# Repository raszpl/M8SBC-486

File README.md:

# M8SBC-486

All the sources (Schematics, PCB, VHDL, BIOS sources) for the M8SBC-486. 

This project is a 486 Homebrew computer, with some efforts to make it kinda PC compatible. See [my page about it](https://maniek86.xyz/projects/m8sbc_486.php).

## Specs:

- 150*150mm 4 layer PCB
- PGA-168 socket for 5V 486 CPUs.
- Xilinx Spartan II XC2S100 FPGA as "chipset". Codename "Hamster 1"
- 4MB SRAM, (8*HM628512)
- 256KB of ROM (W29C020 or 39SF020A) (224 KB accessible)
- 8254 Programmable Interval Timer
- 8259 Programmable Interrupt Controller
- Two 16-bit ISA slots
- PS/2 Keyboard port. Controller is implemented in the FPGA
- Simple CMOS RTC and CMOS storage. Implemented in the FPGA too
- ATMega128 as reset circuit handler, nonvolatile CMOS storage and bitstream loader.

The FSB frequency is currently set to a fixed 24 MHz (DX2 CPUs run then at 48 MHz), but this can be changed by uncommenting/commenting lines in the FPGA source.

Secondary PIC and DMA are missing, so the compatibility is not full. The missing DMA especially breaks support for sound cards.

## Current progress:

The hardware and FPGA are mostly done. BIOS is capable of booting DOS. There are a few issues & bugs, but they are being slowly fixed.

Among the most impressive things the board (as time of writing: 14/03/2026) is capable of: 

- Booting Linux (2.2.26) ([using custom bootloader](https://github.com/maniekx86/linux_m8sbc_boot))

- Booting MS-DOS and FreeDOS: The software compatibility is mixed. Some software hangs the system, throws exceptions, but some run fine. Most notable are: Second Reality demo (no sound), Prince of Persia, Wolfenstein 3D, Fasttracker II (PC speaker works in one mode, LPT DAC works okay), 3DBench 1.0c, CACHECHK.

- Running DOOM ([FastDOOM](https://github.com/viti95/FastDoom) running on FreeDOS 1.4)

## Hardware diagram

<hr>

## Special thanks to [PCBWay](https://www.pcbway.com)!

Special thanks to PCBWay for sponsoring PCBs for this project! Their sponsorship was a huge help and enabled me to make progress with this project. PCBWay is a well-known PCB prototyping and manufacturing service, providing high-quality boards and excellent customer support. I have worked with their boards in the past and can say that they are of great quality. I easily placed an order for PCBs on their platform for this project without any problems. The sponsorship also included a free quick delivery option. If you’re looking for reliable PCB prototyping and manufacturing services, I highly recommend [checking them](https://www.pcbway.com).

# Folders

## pcb/

Schematic and PCB design for this homebrew computer. Board is 150mm*150mm with 4 layers. (Placement of the screw holes is not compliant with any standard)

## chipset/

Sources for the "Hamster 1" chipset. FPGA used is XC2S100 (Xilinx Spartan II). Compile with Xilinx ISE 10.1

## avr/

Sources for AVR ATMega128:

Small AVR firmware that configures the FPGA from on-chip flash at power-up and manages system reset for the M8SBC-486 project

## bios/

M8SBC-486 SeaPig BIOS

Based on this project: [b-dmitry1/BIOS](https://github.com/b-dmitry1/BIOS)

## Disclaimer

This project is essentially my hobby, as I like retro, electronics, digital circuits and low-level programming. I never expected this computer to run DOS in the first place. I consider it pretty much experimental and made to research the workings of older x86 chips. I am pretty sure that this work could be used to build something more robust and stable or even to develop fully custom-made boards for other x86 CPUs. It took me a lot of time, but I don't regret it. There are still many issues, but it's heartwarming that I can get so much existing software to work. And, thanks to everyone for support!

## Acknowledgements

Special thanks to: TheRetroWeb community, [b-dmitry1](https://github.com/b-dmitry1) and [PCBWay](https://pcbway.com/)

## More images

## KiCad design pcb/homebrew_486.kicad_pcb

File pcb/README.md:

### Images

# M8SBC-486 PCB

M8SBC-486 KiCad 9.0 schematic. Current revision: 1.01

Used fonts: Ac437 IBM VGA 8x16 and URW Gothic

## Acknowledgements

- 486 Socket symbol & footprint: [ciprian-stingu/KiCad-486-CPU-socket](https://github.com/ciprian-stingu/Kicad-486-CPU-socket)
- Mini DIN-6 connector with shielding footprint: [4x1md/kicad_libraries](https://github.com/4x1md/kicad_libraries)
- 16-bit ISA slot footprint: [the retro web / Aries-1](https://gitlab.com/ultimateretro/aries-1/)
- [PCBWay](https://www.pcbway.com/) for manufacturing boards!

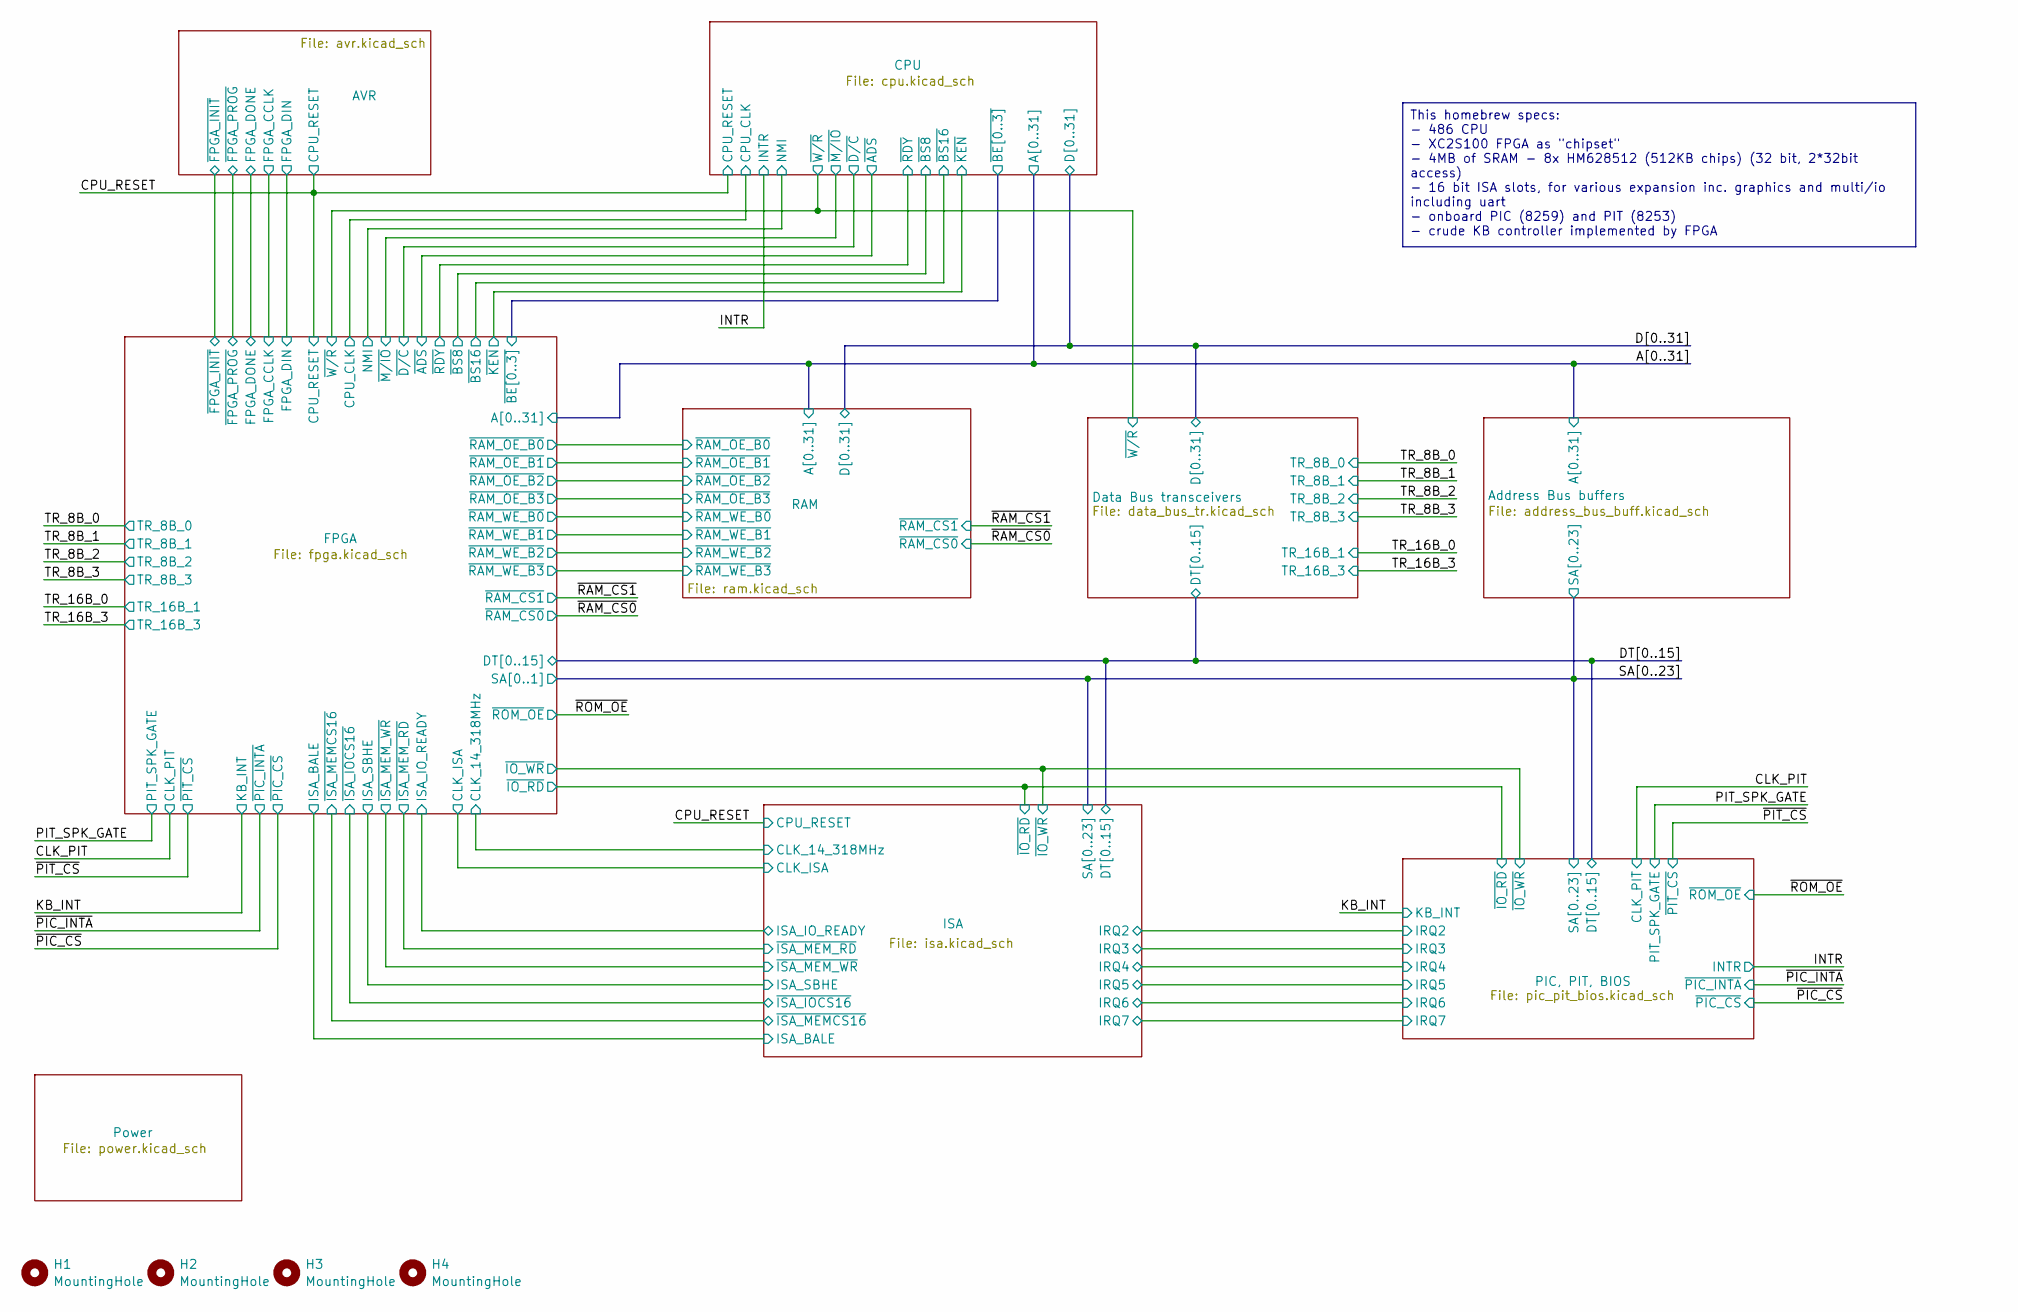
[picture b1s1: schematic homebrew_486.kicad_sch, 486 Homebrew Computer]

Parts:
H1, H2, H3, H4: MountingHole; MountingHole_4mm

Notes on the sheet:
This homebrew specs: - 486 CPU - XC2S100 FPGA as "chipset" - 4MB of SRAM - 8x HM628512 (512KB chips) (32 bit, 2*32bit access) - 16 bit ISA slots, for various expansion inc. graphics and multi/io including uart - onboard PIC (8259) and PIT (8253) - crude KB controller implemented by FPGA

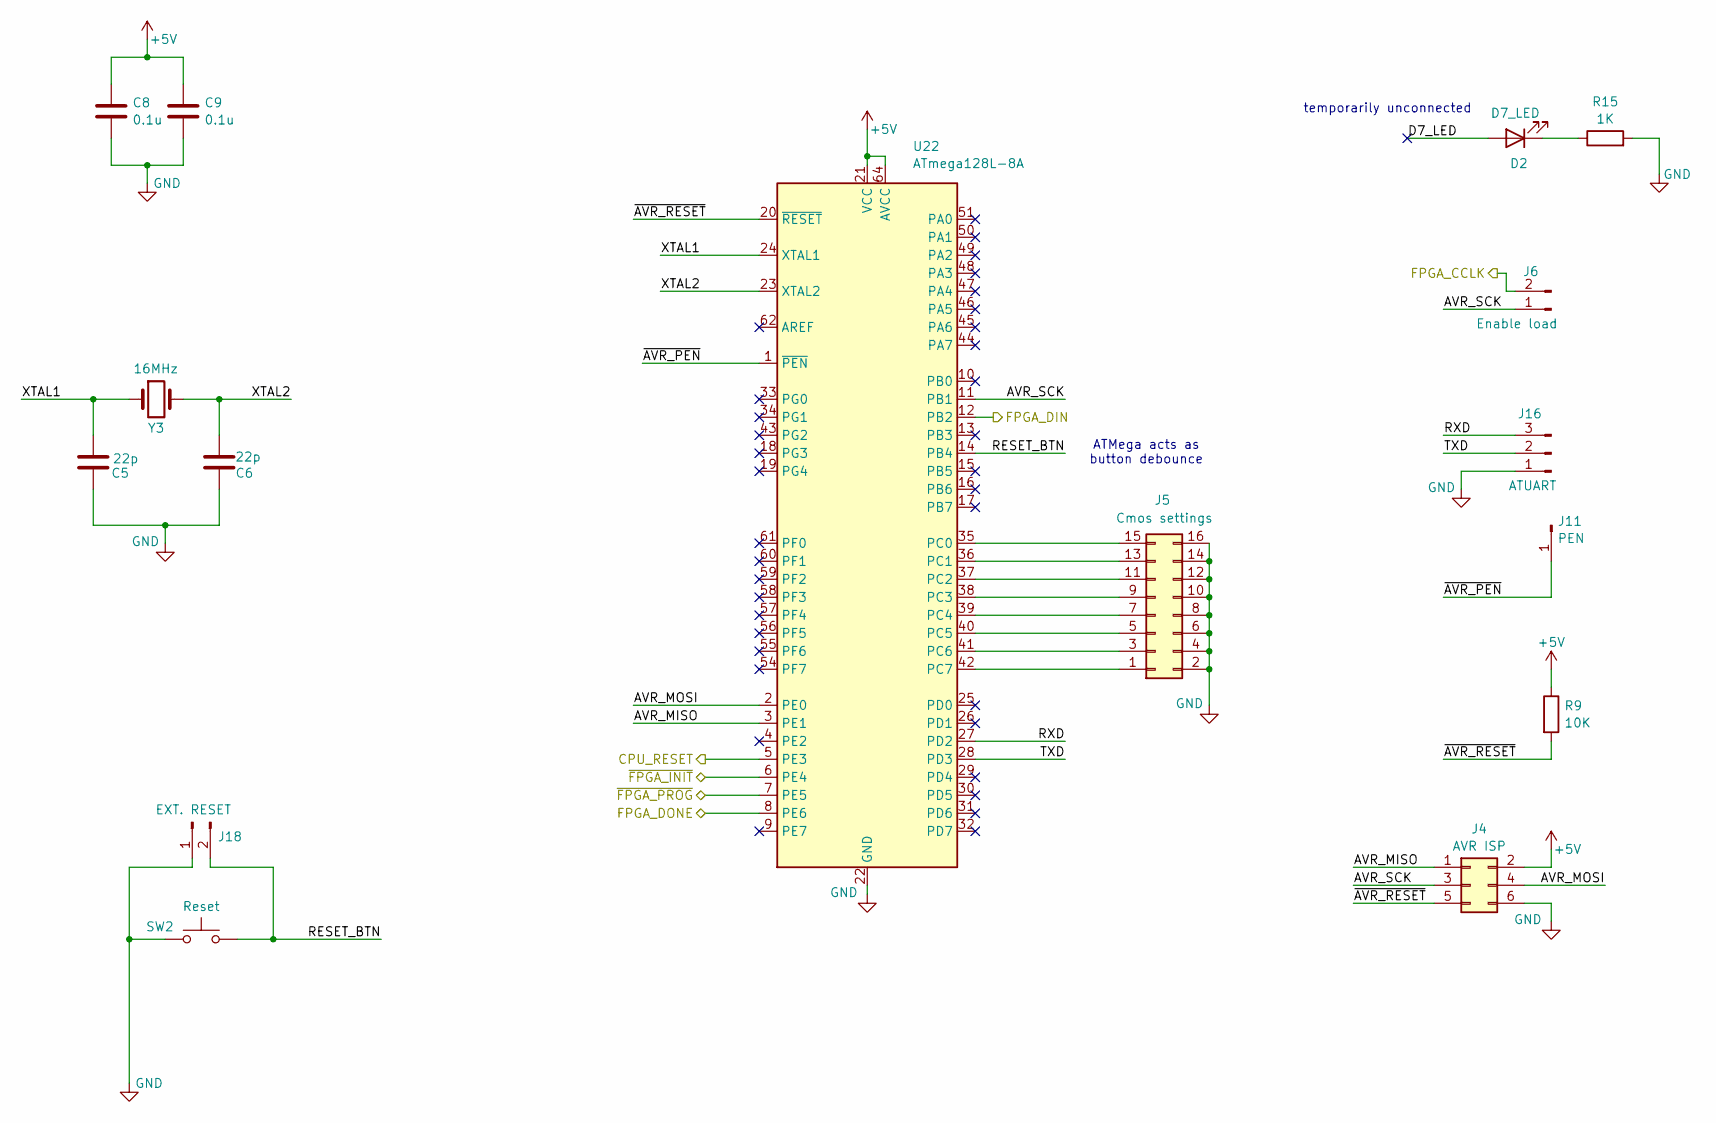
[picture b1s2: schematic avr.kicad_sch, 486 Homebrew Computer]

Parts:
C5, C6: 22p; C_0805_2012Metric_Pad1.18x1.45mm_HandSolder
C8, C9: 0.1u; C_0805_2012Metric_Pad1.18x1.45mm_HandSolder
D2: D7_LED; LED_D4.0mm
J4: AVR ISP; PinHeader_2x03_P2.54mm_Vertical
J5: Cmos settings; PinHeader_2x08_P2.54mm_Vertical
J6: Enable load; PinHeader_1x02_P2.54mm_Vertical
J11: PEN; PinHeader_1x01_P2.54mm_Vertical
J16: ATUART; PinHeader_1x03_P2.54mm_Vertical
J18: EXT. RESET; PinHeader_1x02_P2.54mm_Vertical
R9: 10K; R_0805_2012Metric_Pad1.20x1.40mm_HandSolder
R15: 1K; R_0805_2012Metric_Pad1.20x1.40mm_HandSolder
SW2: Reset; SW_PUSH_6mm
U22: ATmega128L-8A; TQFP-64_14x14mm_P0.8mm
Y3: 16MHz; Crystal_HC49-4H_Vertical

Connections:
+5V: C8.2, C9.2, J4.2, R9.1, U22.21 (VCC), U22.52 (VCC), U22.64 (AVCC); also elsewhere on the board
/AVR/AVR_MISO: J4.1, U22.3 (PE1)
/AVR/AVR_MOSI: J4.4, U22.2 (PE0)
/AVR/AVR_SCK: J4.3, J6.1, U22.11 (PB1)
/AVR/D7_LED: D2.2 (A)
/AVR/FPGA_CCLK: J6.2; also elsewhere on the board
/AVR/FPGA_DIN: U22.12 (PB2); also elsewhere on the board
/AVR/FPGA_DONE: U22.8 (PE6); also elsewhere on the board
/AVR/RESET_BTN: J18.2, SW2.2, U22.14 (PB4)
/AVR/RXD: J16.3, U22.27 (PD2)
/AVR/TXD: J16.2, U22.28 (PD3)
/AVR/XTAL1: C5.2, U22.24 (XTAL1), Y3.1
/AVR/XTAL2: C6.2, U22.23 (XTAL2), Y3.2
/AVR/~AVR_PEN: J11.1 (Pin_1_1), U22.1 (~PEN)
/AVR/~AVR_RESET: J4.5, R9.2, U22.20 (~RESET)
/AVR/~FPGA_INIT: U22.6 (PE4); also elsewhere on the board
/AVR/~FPGA_PROG: U22.7 (PE5); also elsewhere on the board
/CPU_RESET: U22.5 (PE3); also elsewhere on the board
GND: C5.1, C6.1, C8.1, C9.1, J4.6, J5.2, J5.4, J5.6, J5.8, J5.10, J5.12, J5.14, J5.16, J16.1, J18.1, R15.2, SW2.1, U22.22 (GND), U22.53 (GND), U22.63 (GND); also elsewhere on the board
unnamed: D2.1 (K), R15.1
unnamed: J5.1, U22.42 (PC7)
unnamed: J5.3, U22.41 (PC6)
unnamed: J5.5, U22.40 (PC5)
unnamed: J5.7, U22.39 (PC4)
unnamed: J5.9, U22.38 (PC3)
unnamed: J5.11, U22.37 (PC2)
unnamed: J5.13, U22.36 (PC1)
unnamed: J5.15, U22.35 (PC0)

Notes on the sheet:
temporarily unconnected
ATMega acts as button debounce

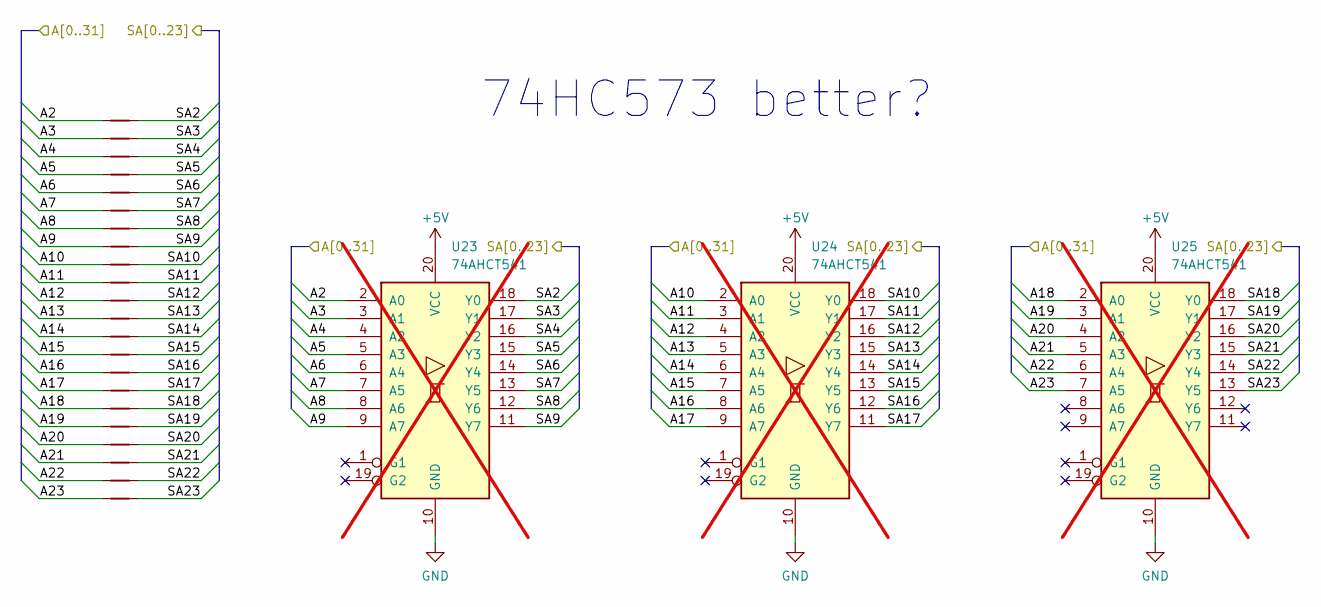
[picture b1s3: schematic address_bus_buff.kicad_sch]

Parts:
NT1, NT2, NT3, NT7, NT8, NT9, NT10, NT11, NT12, NT13, NT14, NT15, NT16, NT17, NT18, NT19, NT20, NT21, NT22, NT23, NT24, NT25: NetTie_2; NetTie-2_SMD_Pad0.16mm
U23: 74AHCT541; SSOP-20_5.3x7.2mm_P0.65mm; not fitted
U24, U25: 74AHCT541; not fitted

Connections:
/A2: NT7.1, U23.2 (A0); also elsewhere on the board
/A3: NT8.1, U23.3 (A1); also elsewhere on the board
/A4: NT9.1, U23.4 (A2); also elsewhere on the board
/A5: NT10.1, U23.5 (A3); also elsewhere on the board
/A6: NT11.1, U23.6 (A4); also elsewhere on the board
/A7: NT12.1, U23.7 (A5); also elsewhere on the board
/A8: NT13.1, U23.8 (A6); also elsewhere on the board
/A9: NT14.1, U23.9 (A7); also elsewhere on the board
/A10: NT15.1, U24.2 (A0); also elsewhere on the board
/A11: NT16.1, U24.3 (A1); also elsewhere on the board
/A12: NT17.1, U24.4 (A2); also elsewhere on the board
/A13: NT18.1, U24.5 (A3); also elsewhere on the board
/A14: NT19.1, U24.6 (A4); also elsewhere on the board
/A15: NT20.1, U24.7 (A5); also elsewhere on the board
/A16: NT21.1, U24.8 (A6); also elsewhere on the board
/A17: NT22.1, U24.9 (A7); also elsewhere on the board
/A18: NT23.1, U25.2 (A0); also elsewhere on the board
/A19: NT24.1, U25.3 (A1); also elsewhere on the board
/A20: NT25.1, U25.4 (A2); also elsewhere on the board
/A21: NT1.1, U25.5 (A3); also elsewhere on the board
/A22: NT2.1, U25.6 (A4); also elsewhere on the board
/A23: NT3.1, U25.7 (A5); also elsewhere on the board
/SA2: NT7.2, U23.18 (Y0); also elsewhere on the board
/SA3: NT8.2, U23.17 (Y1); also elsewhere on the board
/SA4: NT9.2, U23.16 (Y2); also elsewhere on the board
/SA5: NT10.2, U23.15 (Y3); also elsewhere on the board
/SA6: NT11.2, U23.14 (Y4); also elsewhere on the board
/SA7: NT12.2, U23.13 (Y5); also elsewhere on the board
/SA8: NT13.2, U23.12 (Y6); also elsewhere on the board
/SA9: NT14.2, U23.11 (Y7); also elsewhere on the board
/SA10: NT15.2, U24.18 (Y0); also elsewhere on the board
/SA11: NT16.2, U24.17 (Y1); also elsewhere on the board
/SA12: NT17.2, U24.16 (Y2); also elsewhere on the board
/SA13: NT18.2, U24.15 (Y3); also elsewhere on the board
/SA14: NT19.2, U24.14 (Y4); also elsewhere on the board
/SA15: NT20.2, U24.13 (Y5); also elsewhere on the board
/SA16: NT21.2, U24.12 (Y6); also elsewhere on the board
/SA17: NT22.2, U24.11 (Y7); also elsewhere on the board
/SA18: NT23.2, U25.18 (Y0); also elsewhere on the board
/SA19: NT24.2, U25.17 (Y1); also elsewhere on the board
/SA20: NT25.2, U25.16 (Y2); also elsewhere on the board
/SA21: NT1.2, U25.15 (Y3); also elsewhere on the board
/SA22: NT2.2, U25.14 (Y4); also elsewhere on the board
/SA23: NT3.2, U25.13 (Y5); also elsewhere on the board
unnamed: U23.10 (GND), U24.10 (GND), U25.10 (GND)
unnamed: U23.20 (VCC), U24.20 (VCC), U25.20 (VCC)

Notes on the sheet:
74HC573 better?

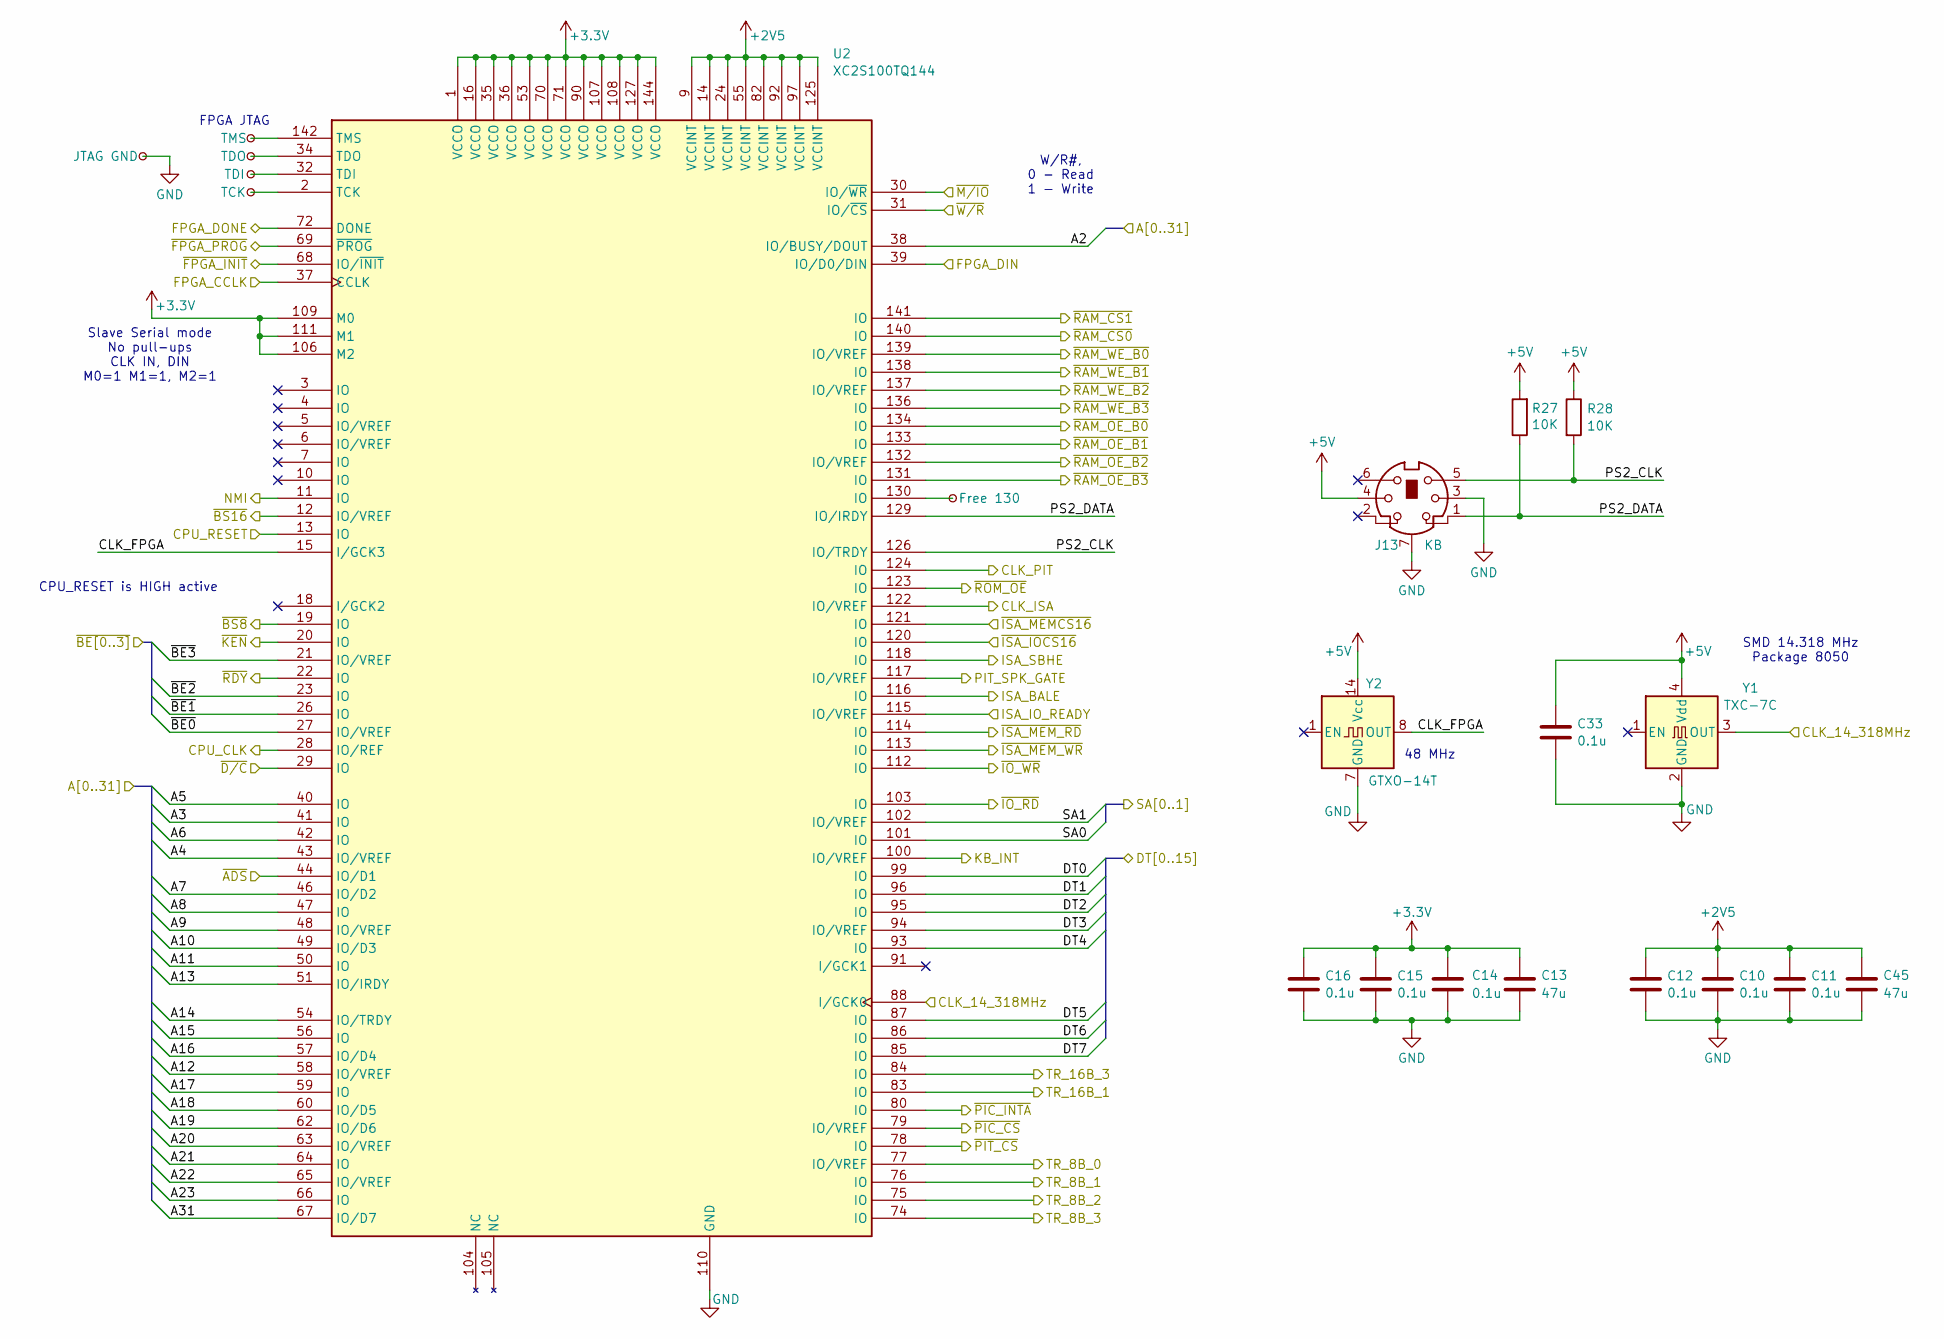
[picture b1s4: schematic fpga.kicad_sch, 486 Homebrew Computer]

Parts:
C10, C11, C12, C14, C15, C16, C33: 0.1u; C_0805_2012Metric_Pad1.18x1.45mm_HandSolder
C13, C45: 47u; C_1210_3225Metric
J13: KB; Connector_Mini-DIN_Female_6Pin_2rows
R27, R28: 10K; R_0805_2012Metric_Pad1.20x1.40mm_HandSolder
TP1: TDO; TestPoint_Pad_D0.4mm
TP2: TDI; TestPoint_Pad_D0.4mm
TP3: TMS; TestPoint_Pad_D0.4mm
TP4: TCK; TestPoint_Pad_D0.4mm
TP5: JTAG GND; TestPoint_Pad_D0.4mm
TP16: Free 130; TestPoint_Pad_D0.4mm
U2: XC2S100TQ144; TQFP-144_20x20mm_P0.5mm
Y1: TXC-7C; Oscillator_SMD_SeikoEpson_SG8002CA-4Pin_7.0x5.0mm_HandSolde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
Y2: GTXO-14T; Oscillator_DIP-14

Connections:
+2V5: C10.2, C11.2, C12.2, C45.2, U2.9 (VCCINT), U2.14 (VCCINT), U2.24 (VCCINT), U2.55 (VCCINT), U2.82 (VCCINT), U2.92 (VCCINT), U2.97 (VCCINT), U2.125 (VCCINT); also elsewhere on the board
+3.3V: C13.2, C14.2, C15.2, C16.2, U2.1 (VCCO), U2.16 (VCCO), U2.35 (VCCO), U2.36 (VCCO), U2.53 (VCCO), U2.70 (VCCO), U2.71 (VCCO), U2.90 (VCCO), U2.106 (M2), U2.107 (VCCO), U2.108 (VCCO), U2.109 (M0), U2.111 (M1), U2.127 (VCCO), U2.144 (VCCO); also elsewhere on the board
+5V: C33.2, J13.4, R27.2, R28.1, Y1.4 (Vdd), Y2.14 (Vcc); also elsewhere on the board
/A2: U2.38 (IO/BUSY/DOUT); also elsewhere on the board
/A3: U2.41 (IO); also elsewhere on the board
/A4: U2.43 (IO/VREF); also elsewhere on the board
/A5: U2.40 (IO); also elsewhere on the board
/A6: U2.42 (IO); also elsewhere on the board
/A7: U2.46 (IO/D2); also elsewhere on the board
/A8: U2.47 (IO); also elsewhere on the board
/A9: U2.48 (IO/VREF); also elsewhere on the board
/A10: U2.49 (IO/D3); also elsewhere on the board
/A11: U2.50 (IO); also elsewhere on the board
/A12: U2.58 (IO/VREF); also elsewhere on the board
/A13: U2.51 (IO/IRDY); also elsewhere on the board
/A14: U2.54 (IO/TRDY); also elsewhere on the board
/A15: U2.56 (IO); also elsewhere on the board
/A16: U2.57 (IO/D4); also elsewhere on the board
/A17: U2.59 (IO); also elsewhere on the board
/A18: U2.60 (IO/D5); also elsewhere on the board
/A19: U2.62 (IO/D6); also elsewhere on the board
/A20: U2.63 (IO/VREF); also elsewhere on the board
/A21: U2.64 (IO); also elsewhere on the board
/A22: U2.65 (IO/VREF); also elsewhere on the board
/A23: U2.66 (IO); also elsewhere on the board
/A31: U2.67 (IO/D7); also elsewhere on the board
/AVR/FPGA_CCLK: U2.37 (CCLK); also elsewhere on the board
/AVR/FPGA_DIN: U2.39 (IO/D0/DIN); also elsewhere on the board
/AVR/FPGA_DONE: U2.72 (DONE); also elsewhere on the board
/AVR/~FPGA_INIT: U2.68 (IO/~INIT); also elsewhere on the board
/AVR/~FPGA_PROG: U2.69 (~PROG); also elsewhere on the board
/CLK_PIT: U2.124 (IO); also elsewhere on the board
/CPU/CPU_CLK: U2.28 (IO/REF); also elsewhere on the board
/CPU/NMI: U2.11 (IO); also elsewhere on the board
/CPU/~ADS: U2.44 (IO/D1); also elsewhere on the board
/CPU/~BE0: U2.27 (IO/VREF); also elsewhere on the board
/CPU/~BE1: U2.26 (IO); also elsewhere on the board
/CPU/~BE2: U2.23 (IO); also elsewhere on the board
/CPU/~BE3: U2.21 (IO/VREF); also elsewhere on the board
/CPU/~BS8: U2.19 (IO); also elsewhere on the board
/CPU/~BS16: U2.12 (IO/VREF); also elsewhere on the board
/CPU/~D/C: U2.29 (IO); also elsewhere on the board
/CPU/~KEN: U2.20 (IO); also elsewhere on the board
/CPU/~M/IO: U2.30 (IO/~WR); also elsewhere on the board
/CPU/~RDY: U2.22 (IO); also elsewhere on the board
/CPU/~W/R: U2.31 (IO/~CS); also elsewhere on the board
/CPU_RESET: U2.13 (IO); also elsewhere on the board
/DT0: U2.99 (IO); also elsewhere on the board
/DT1: U2.96 (IO); also elsewhere on the board
/DT2: U2.95 (IO); also elsewhere on the board
/DT3: U2.94 (IO/VREF); also elsewhere on the board
/DT4: U2.93 (IO); also elsewhere on the board
/DT5: U2.87 (IO); also elsewhere on the board
/DT6: U2.86 (IO); also elsewhere on the board
/DT7: U2.85 (IO); also elsewhere on the board
/FPGA/CLK_14_318MHz: U2.88 (I/GCK0), Y1.3 (OUT); also elsewhere on the board
/FPGA/CLK_FPGA: U2.15 (I/GCK3), Y2.8 (OUT)
/FPGA/CLK_ISA: U2.122 (IO/VREF); also elsewhere on the board
/FPGA/ISA_BALE: U2.116 (IO); also elsewhere on the board
/FPGA/ISA_IO_READY: U2.115 (IO/VREF); also elsewhere on the board
/FPGA/ISA_SBHE: U2.118 (IO); also elsewhere on the board
/FPGA/PS2_CLK: J13.5, R28.2, U2.126 (IO/TRDY)
/FPGA/PS2_DATA: J13.1, R27.1, U2.129 (IO/IRDY)
/FPGA/~IO_RD: U2.103 (IO); also elsewhere on the board
/FPGA/~IO_WR: U2.112 (IO); also elsewhere on the board
/FPGA/~ISA_IOCS16: U2.120 (IO); also elsewhere on the board
/FPGA/~ISA_MEMCS16: U2.121 (IO); also elsewhere on the board
/FPGA/~ISA_MEM_RD: U2.114 (IO); also elsewhere on the board
/FPGA/~ISA_MEM_WR: U2.113 (IO); also elsewhere on the board
/FPGA/~RAM_OE_B0: U2.134 (IO); also elsewhere on the board
/FPGA/~RAM_OE_B1: U2.133 (IO); also elsewhere on the board
/FPGA/~RAM_OE_B2: U2.132 (IO/VREF); also elsewhere on the board
/FPGA/~RAM_OE_B3: U2.131 (IO); also elsewhere on the board
/FPGA/~RAM_WE_B0: U2.139 (IO/VREF); also elsewhere on the board
/FPGA/~RAM_WE_B1: U2.138 (IO); also elsewhere on the board
/FPGA/~RAM_WE_B2: U2.137 (IO/VREF); also elsewhere on the board
/FPGA/~RAM_WE_B3: U2.136 (IO); also elsewhere on the board
/KB_INT: U2.100 (IO/VREF); also elsewhere on the board
/PIT_SPK_GATE: U2.117 (IO/VREF); also elsewhere on the board
/SA0: U2.101 (IO); also elsewhere on the board
/SA1: U2.102 (IO/VREF); also elsewhere on the board
/TR_8B_0: U2.77 (IO/VREF); also elsewhere on the board
/TR_8B_1: U2.76 (IO); also elsewhere on the board
/TR_8B_2: U2.75 (IO); also elsewhere on the board
/TR_8B_3: U2.74 (IO); also elsewhere on the board
/TR_16B_0: U2.83 (IO); also elsewhere on the board
/TR_16B_3: U2.84 (IO); also elsewhere on the board
/~PIC_CS: U2.79 (IO/VREF); also elsewhere on the board
/~PIC_INTA: U2.80 (IO); also elsewhere on the board
/~PIT_CS: U2.78 (IO); also elsewhere on the board
/~RAM_CS0: U2.140 (IO); also elsewhere on the board
/~RAM_CS1: U2.141 (IO); also elsewhere on the board
/~ROM_OE: U2.123 (IO); also elsewhere on the board
GND: C10.1, C11.1, C12.1, C13.1, C14.1, C15.1, C16.1, C33.1, C45.1, J13.3, J13.7, TP5.1 (1_1), U2.8 (GND), U2.17 (GND), U2.25 (GND), U2.33 (GND), U2.45 (GND), U2.52 (GND), U2.61 (GND), U2.73 (GND), U2.81 (GND), U2.89 (GND), U2.98 (GND), U2.110 (GND), U2.119 (GND), U2.128 (GND), U2.135 (GND), U2.143 (GND), Y1.2 (GND), Y2.7 (GND); also elsewhere on the board
unnamed: TP16.1 (1_1), U2.130 (IO)
unnamed: TP4.1 (1_1), U2.2 (TCK)
unnamed: TP2.1 (1_1), U2.32 (TDI)
unnamed: TP1.1 (1_1), U2.34 (TDO)
unnamed: TP3.1 (1_1), U2.142 (TMS)

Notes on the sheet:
W/R#, 0 - Read 1 - Write
CPU_RESET is HIGH active
Slave Serial mode No pull-ups CLK IN, DIN M0=1 M1=1, M2=1
48 MHz
SMD 14.318 MHz Package 8050
FPGA JTAG

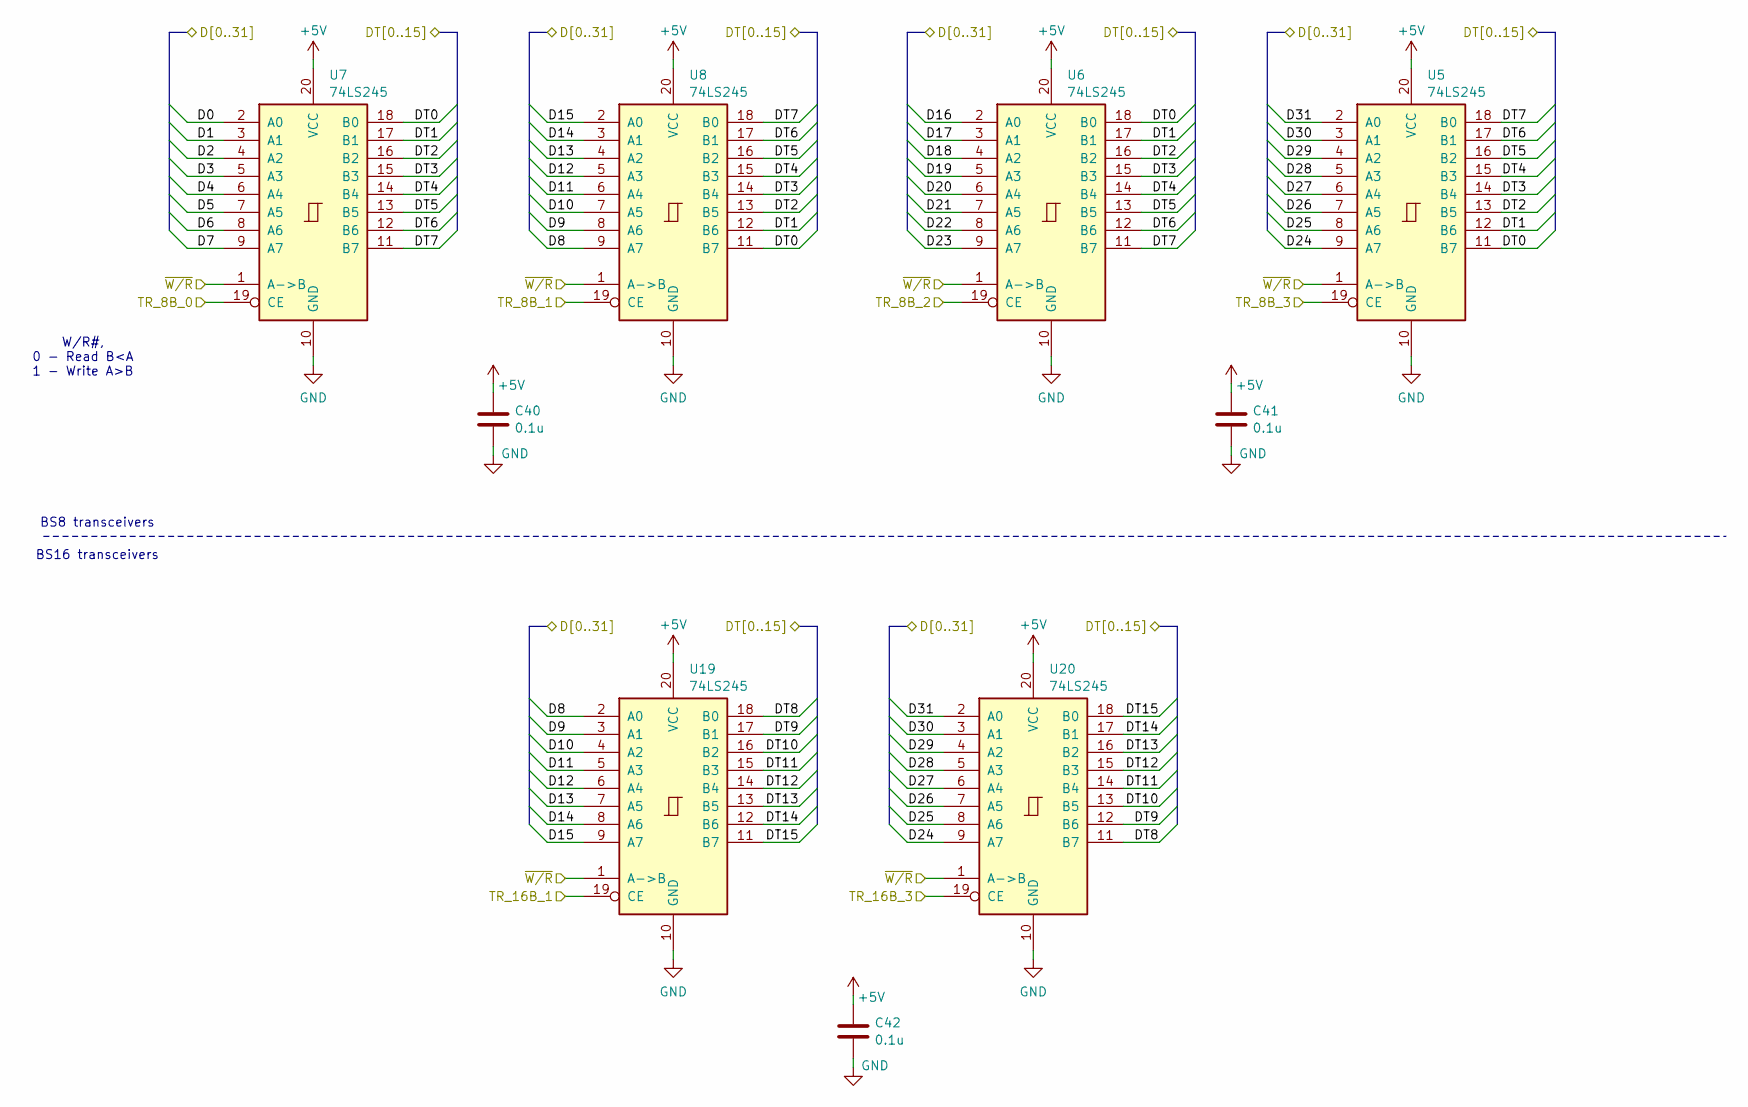
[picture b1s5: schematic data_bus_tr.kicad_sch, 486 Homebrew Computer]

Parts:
C40, C41, C42: 0.1u; C_0805_2012Metric_Pad1.18x1.45mm_HandSolder
U5, U6, U7, U8, U19, U20: 74LS245; SOP-20_7.5x12.8mm_P1.27mm

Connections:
+5V: C40.2, C41.2, C42.2, U5.20 (VCC), U6.20 (VCC), U7.20 (VCC), U8.20 (VCC), U19.20 (VCC), U20.20 (VCC); also elsewhere on the board
/CPU/~W/R: U5.1 (A->B), U6.1 (A->B), U7.1 (A->B), U8.1 (A->B), U19.1 (A->B), U20.1 (A->B); also elsewhere on the board
/D0: U7.2 (A0); also elsewhere on the board
/D1: U7.3 (A1); also elsewhere on the board
/D2: U7.4 (A2); also elsewhere on the board
/D3: U7.5 (A3); also elsewhere on the board
/D4: U7.6 (A4); also elsewhere on the board
/D5: U7.7 (A5); also elsewhere on the board
/D6: U7.8 (A6); also elsewhere on the board
/D7: U7.9 (A7); also elsewhere on the board
/D8: U8.9 (A7), U19.2 (A0); also elsewhere on the board
/D9: U8.8 (A6), U19.3 (A1); also elsewhere on the board
/D10: U8.7 (A5), U19.4 (A2); also elsewhere on the board
/D11: U8.6 (A4), U19.5 (A3); also elsewhere on the board
/D12: U8.5 (A3), U19.6 (A4); also elsewhere on the board
/D13: U8.4 (A2), U19.7 (A5); also elsewhere on the board
/D14: U8.3 (A1), U19.8 (A6); also elsewhere on the board
/D15: U8.2 (A0), U19.9 (A7); also elsewhere on the board
/D16: U6.2 (A0); also elsewhere on the board
/D17: U6.3 (A1); also elsewhere on the board
/D18: U6.4 (A2); also elsewhere on the board
/D19: U6.5 (A3); also elsewhere on the board
/D20: U6.6 (A4); also elsewhere on the board
/D21: U6.7 (A5); also elsewhere on the board
/D22: U6.8 (A6); also elsewhere on the board
/D23: U6.9 (A7); also elsewhere on the board
/D24: U5.9 (A7), U20.9 (A7); also elsewhere on the board
/D25: U5.8 (A6), U20.8 (A6); also elsewhere on the board
/D26: U5.7 (A5), U20.7 (A5); also elsewhere on the board
/D27: U5.6 (A4), U20.6 (A4); also elsewhere on the board
/D28: U5.5 (A3), U20.5 (A3); also elsewhere on the board
/D29: U5.4 (A2), U20.4 (A2); also elsewhere on the board
/D30: U5.3 (A1), U20.3 (A1); also elsewhere on the board
/D31: U5.2 (A0), U20.2 (A0); also elsewhere on the board
/DT0: U5.11 (B7), U6.18 (B0), U7.18 (B0), U8.11 (B7); also elsewhere on the board
/DT1: U5.12 (B6), U6.17 (B1), U7.17 (B1), U8.12 (B6); also elsewhere on the board
/DT2: U5.13 (B5), U6.16 (B2), U7.16 (B2), U8.13 (B5); also elsewhere on the board
/DT3: U5.14 (B4), U6.15 (B3), U7.15 (B3), U8.14 (B4); also elsewhere on the board
/DT4: U5.15 (B3), U6.14 (B4), U7.14 (B4), U8.15 (B3); also elsewhere on the board
/DT5: U5.16 (B2), U6.13 (B5), U7.13 (B5), U8.16 (B2); also elsewhere on the board
/DT6: U5.17 (B1), U6.12 (B6), U7.12 (B6), U8.17 (B1); also elsewhere on the board
/DT7: U5.18 (B0), U6.11 (B7), U7.11 (B7), U8.18 (B0); also elsewhere on the board
/DT8: U19.18 (B0), U20.11 (B7); also elsewhere on the board
/DT9: U19.17 (B1), U20.12 (B6); also elsewhere on the board
/DT10: U19.16 (B2), U20.13 (B5); also elsewhere on the board
/DT11: U19.15 (B3), U20.14 (B4); also elsewhere on the board
/DT12: U19.14 (B4), U20.15 (B3); also elsewhere on the board
/DT13: U19.13 (B5), U20.16 (B2); also elsewhere on the board
/DT14: U19.12 (B6), U20.17 (B1); also elsewhere on the board
/DT15: U19.11 (B7), U20.18 (B0); also elsewhere on the board
/TR_8B_0: U7.19 (CE); also elsewhere on the board
/TR_8B_1: U8.19 (CE); also elsewhere on the board
/TR_8B_2: U6.19 (CE); also elsewhere on the board
/TR_8B_3: U5.19 (CE); also elsewhere on the board
/TR_16B_0: U19.19 (CE); also elsewhere on the board
/TR_16B_3: U20.19 (CE); also elsewhere on the board
GND: C40.1, C41.1, C42.1, U5.10 (GND), U6.10 (GND), U7.10 (GND), U8.10 (GND), U19.10 (GND), U20.10 (GND); also elsewhere on the board

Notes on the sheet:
W/R#, 0 - Read B<A 1 - Write A>B
BS8 transceivers
BS16 transceivers
